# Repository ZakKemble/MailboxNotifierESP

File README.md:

# Mail Notifier - WiFi Edition

Basically just a WiFi version of a previous [mail notifier](https://blog.zakkemble.net/remote-mail-notifier-and-gps-tracker/) project :D

https://blog.zakkemble.net/mail-notifier-wifi-edition/

---

Zak Kemble

contact@zakkemble.net

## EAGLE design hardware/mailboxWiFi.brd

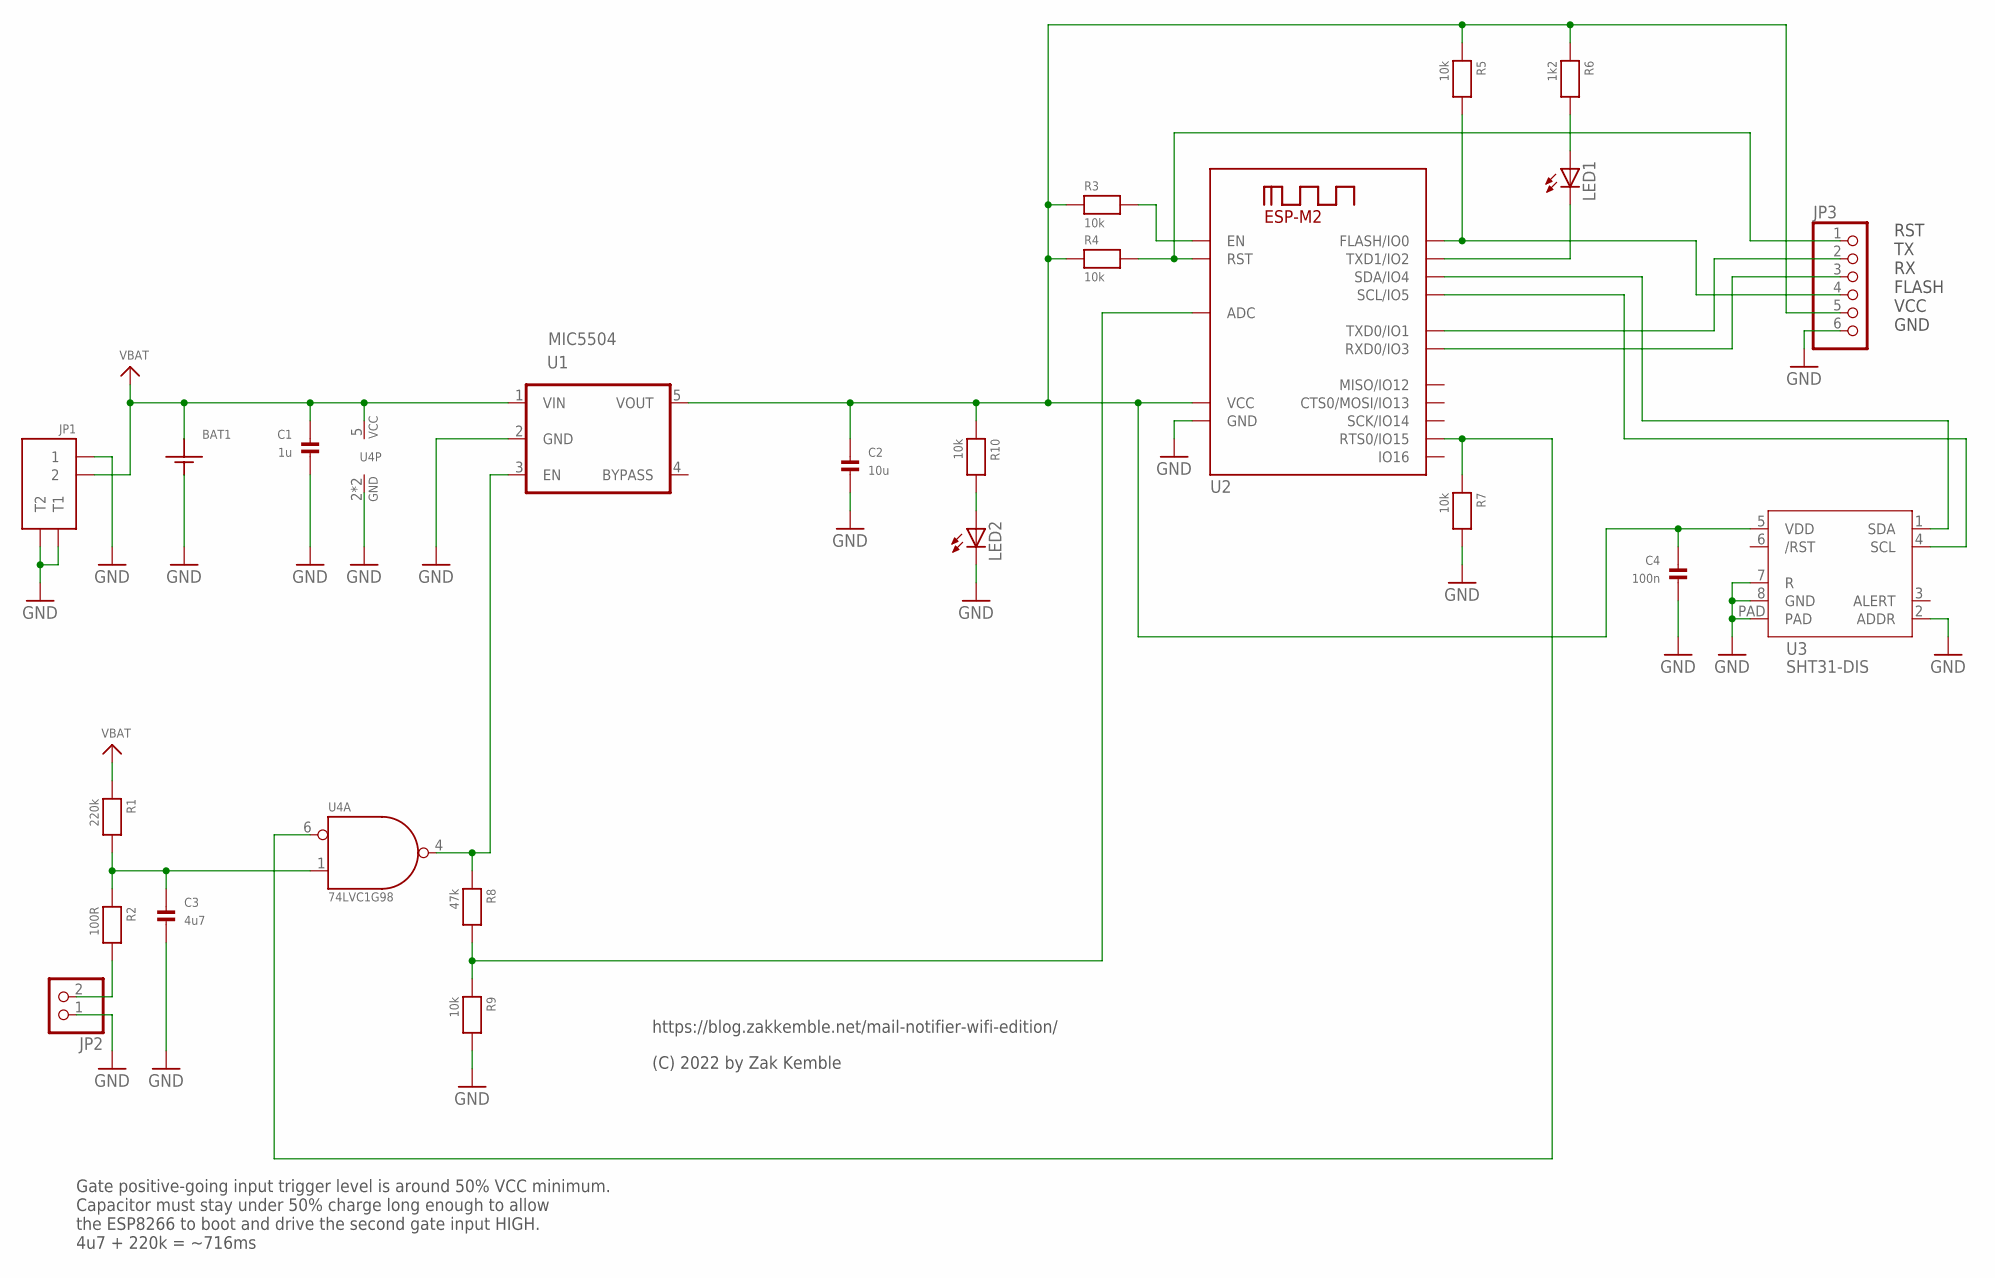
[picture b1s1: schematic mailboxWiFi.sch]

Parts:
BAT1: BATTERY_HOLDER1XAAA_PCB; BATT_HOLDER_AAA_PCB
C1: 1u; 0805_NO_OUTLINE; FARNELL 2470435
C2: 10u; 1206; FARNELL 9227881,1828814
C3: 4u7; 0805_NO_OUTLINE
C4: 100n; 0402_XSMALL
JP1: 2WAY-SMDVERT; 2WAY-SMD
JP2: PINHD-1X2/90; 1X02/90
JP3: PINHD-1X6; 1X06
LED1, LED2: LED0402_XSMALL; 0402_DIODE_XSMALL
R1: 220k; 0402_XSMALL
R2: 100R; 0402_XSMALL
R3, R4, R5, R7, R9, R10: 10k; 0402_XSMALL
R6: 1k2; 0402_XSMALL
R8: 47k; 0402_XSMALL
U1: MIC5504; SOT23-5_SM_PAD
U2: ESP-M2
U3: SHT31-DIS; DFN_2.5X2.5_8
U4: 74LVC1G98; SOT-363

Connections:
GND: BAT1.NEG, C1.2, C2.2, C3.2, C4.2, JP1.1, JP1.TAB$1 (T1), JP1.TAB$2 (T2), JP2.1, JP3.6, LED2.2 (C), R7.2, R9.2, U1.2 (GND), U2.8 (GND), U3.2 (ADDR), U3.7 (R), U3.8 (GND), U3.PAD, U4.2 (GND), U4.3 (GND)
unnamed: R3.2, U2.2 (EN)
unnamed: U2.12 (SCL/IO5), U3.4 (SCL)
unnamed: U2.11 (SDA/IO4), U3.1 (SDA)
unnamed: JP3.1, R4.2, U2.15 (RST)
unnamed: C2.1, C4.1, JP3.5, R3.1, R4.1, R5.1, R6.1, R10.1, U1.5 (VOUT), U2.7 (VCC), U3.5 (VDD)
unnamed: R8.2, R9.1, U2.1 (ADC)
unnamed: C3.1, R1.2, R2.1, U4.1 (B)
unnamed: JP3.4, R5.2, U2.10 (FLASH/IO0)
unnamed: JP2.2, R2.2
unnamed: R8.1, U1.3 (EN), U4.4 (Y)
unnamed: R7.1, U2.6 (RTS0/IO15), U4.6 (A)
unnamed: LED1.2 (C), U2.9 (TXD1/IO2)
unnamed: LED2.1 (A), R10.2
unnamed: JP3.2, U2.14 (TXD0/IO1)
unnamed: JP3.3, U2.13 (RXD0/IO3)
unnamed: LED1.1 (A), R6.2
VBAT: BAT1.POS, C1.1, JP1.2, R1.1, U1.1 (VIN), U4.5 (VCC)

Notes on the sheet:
RST TX RX FLASH VCC GND
https://blog.zakkemble.net/mail-notifier-wifi-edition/
Gate positive-going input trigger level is around 50% VCC minimum. Capacitor must stay under 50% charge long enough to allow the ESP8266 to boot and drive the second gate input HIGH. 4u7 + 220k = ~716ms
(C) 2022 by Zak Kemble

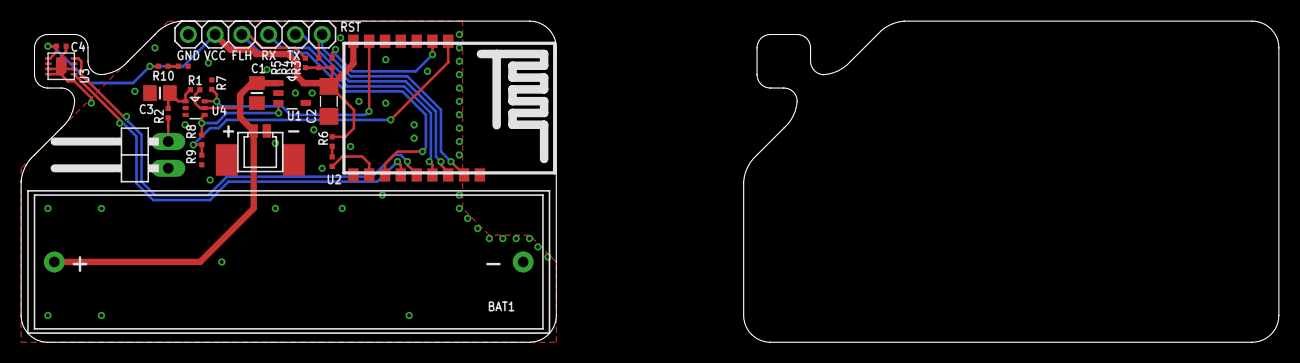
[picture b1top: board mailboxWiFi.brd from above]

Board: 2 copper layers, 119.4 x 30.5 mm, 24 parts (0 on the bottom side), 18 nets.

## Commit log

2022-05-09 Initial commit :bee:
2022-08-10 Simplify PHP script

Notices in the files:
parts and their libraries:
microbuilder: This work is placed in the public domain, and may be freely used for commercial and non-commercial work with the following conditions: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
